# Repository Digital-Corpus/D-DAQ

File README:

D-DAQ
=====
Inspired by a simple, in-cluster, digital boost and EGT gauge created by user Doniol on forums.tdiclub.com.

Features:
3-head, 160x128 OLED displays
14 analog inputs
2 impulse inputs
Data acqusition/logging to microSD card
CAN connectivity
USB connectivity
JTAG header

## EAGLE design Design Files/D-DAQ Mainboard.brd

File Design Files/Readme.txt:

The contents of this zip folder are released under the CERN OHL v1.2
For more information, please visit:
http://www.ohwr.org/projects/cernohl/wiki

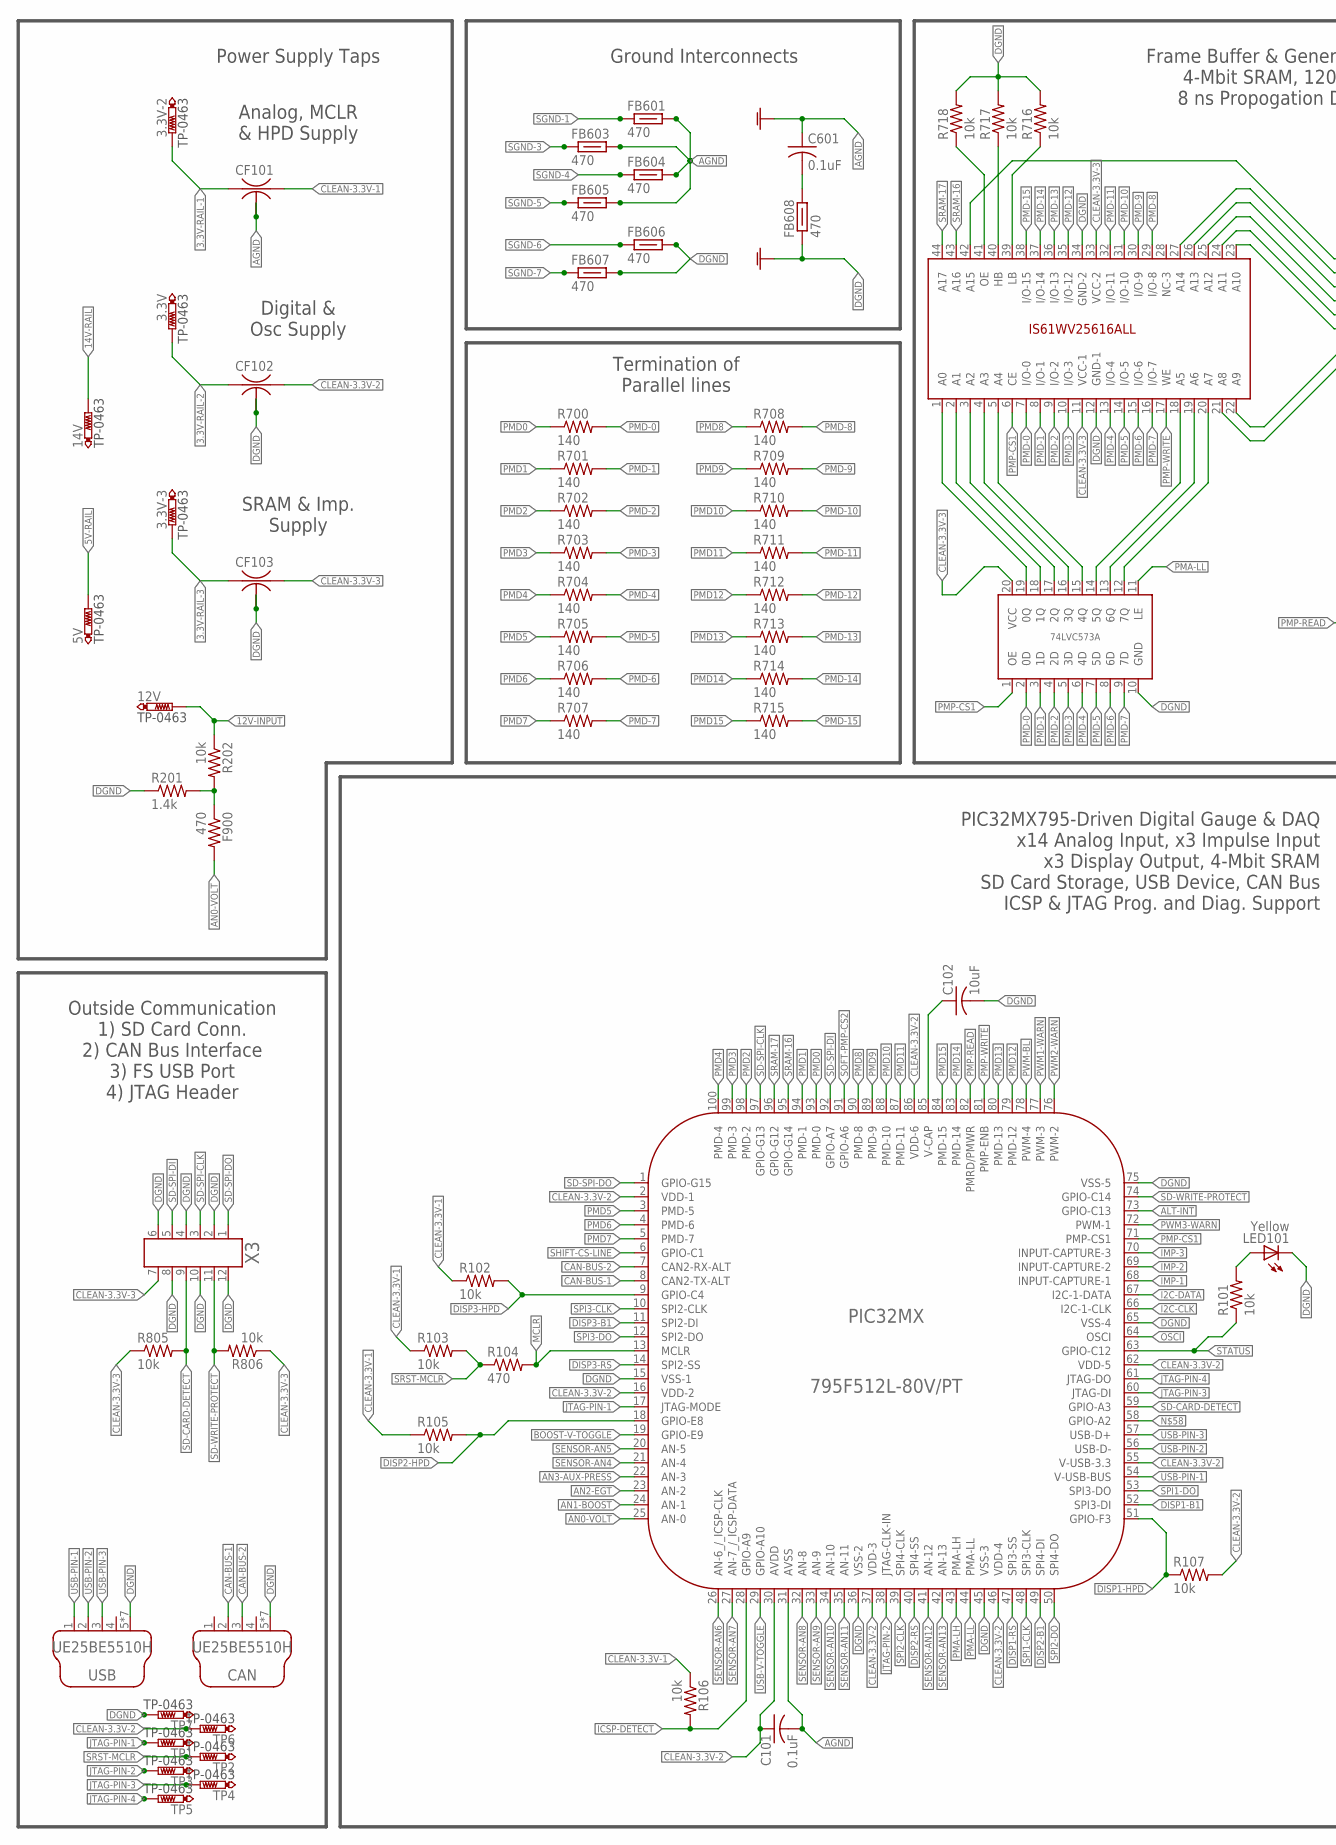
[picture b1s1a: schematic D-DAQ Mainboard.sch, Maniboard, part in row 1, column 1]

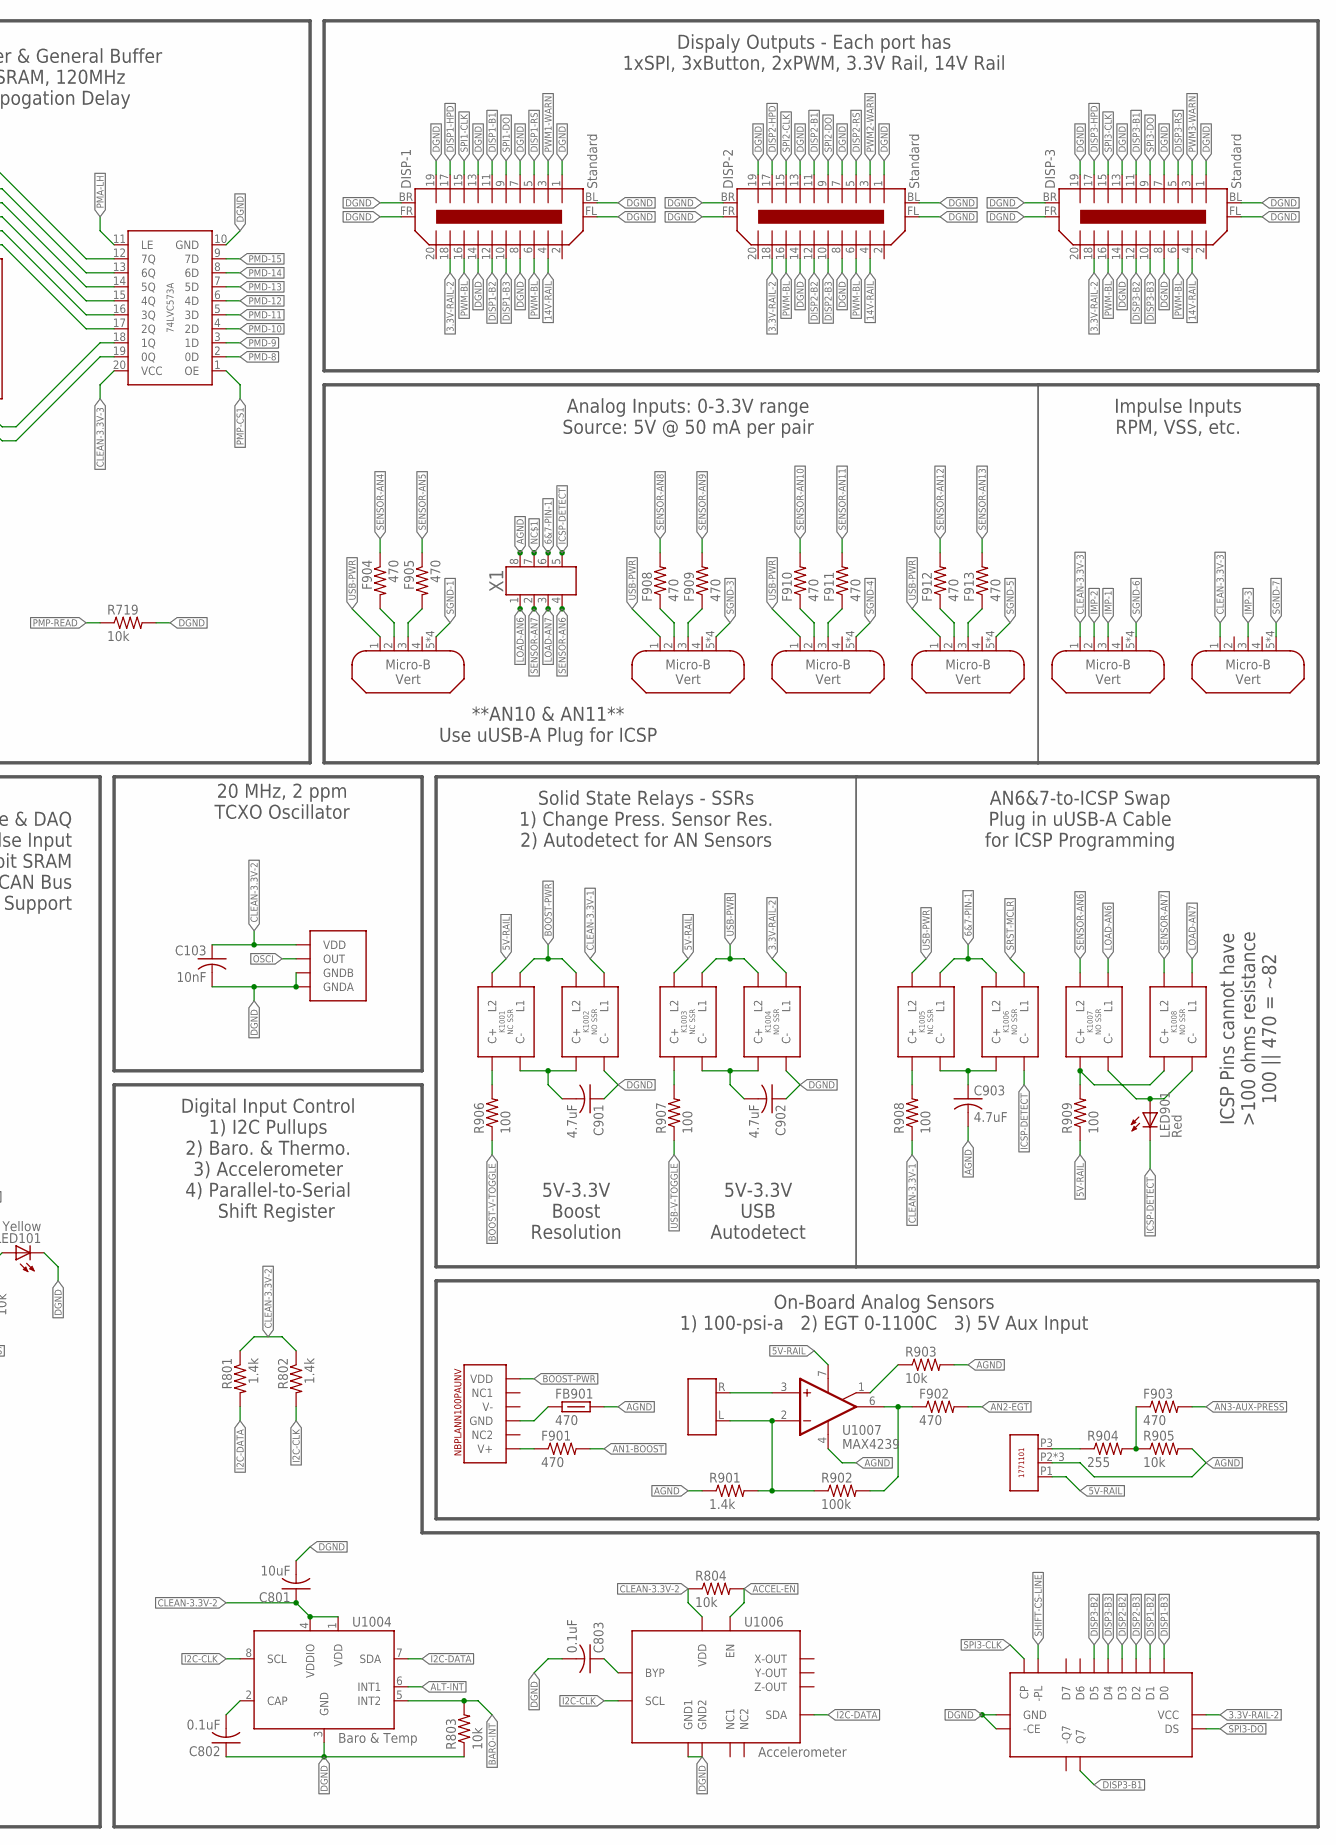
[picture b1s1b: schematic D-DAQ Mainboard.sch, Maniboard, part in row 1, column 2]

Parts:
3.3V, 3.3V-2, 3.3V-3, 5V, 12V, 14V: TP-0463; TP-REC
AUX: PC-3-1771101; PC-1771101
C101, C601, C802, C803: 0.1uF; SMD-0603
C102, C801: 10uF; SMD-0805
C103: 10nF; SMD-0603
C901, C902, C903: 4.7uF; SMD-0603
CAN: UE25BE5510H; USB-MINI-B-VERT
CF101, CF102, CF103: NMF21PS; NFM21PS
DISP-1, DISP-2, DISP-3: Standard; JAE-MDP-STD
EGT: PC-2-1702610; PC-1702610
F900, F901, F902, F903, F904, F905, F908, F909, F910, F911, F912, F913: 470; SMD-0603
FB601, FB603, FB604, FB605, FB606, FB607, FB608, FB901: 470; SMD-0603
IMP-1&2, IMP-3: Micro USB; USB-MICRO-B-VERT
K1001, K1003, K1005: NC SSR; SOP-4-NC
K1002, K1004, K1006, K1007, K1008: NO SSR; SOP-4-NO
LED101: Yellow; SMD-0603
LED901: Red; SMD-0603
MEM1001: IS61WV25616ALL; TSOP-44
P-4&5, P-8&9, P-10&11, P-12&13: Micro USB; USB-MICRO-B-VERT
R101, R102, R103, R105, R106, R107, R202, R716, R717, R718, R719, R803, R804, R805, R806, R903, R905: 10k; SMD-0603
R104: 470; SMD-0603
R201, R801, R802, R901: 1.4k; SMD-0603
R700, R701, R702, R703, R704, R705, R706, R707, R708, R709, R710, R711, R712, R713, R714, R715: 140; SMD-0402
R902: 100k; SMD-0603
R904: 255; SMD-0603
R906, R907, R908, R909: 100; SMD-0603
TP1, TP2, TP3, TP4, TP5, TP6, TP7: TP-0463; TP-REC
U1001: 795F512L-80V/PT; TQFP-100-14X14
U1002, U1003: Octal D-Latch; TSSOP-20
U1004: Baro & Temp; LGA-8
U1005: Boost; LEADLESS-SMT
U1006: Accelerometer; QFN-12
U1007: MAX4239; SOT-8
U1008: NXP-74HC165; DHVQFN16
USB: UE25BE5510H; USB-MINI-B-VERT
X1: MOLEX-87760-0816
X3: MOLEX-87760-1216"; MOLEX-87760-1216
Y1001: XTC7009; 3.2X2.5MM

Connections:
3.3V-RAIL-1: 3.3V-2.TP, CF101.1
3.3V-RAIL-2: 3.3V.TP, CF102.1, DISP-1.18, DISP-2.18, DISP-3.18, K1004.3 (L1), U1008.VCC
3.3V-RAIL-3: 3.3V-3.TP, CF103.1
5V-RAIL: 5V.TP, AUX.P1, K1001.4 (L2), K1003.4 (L2), R909.1, U1007.7 (V+)
6&7-PIN-1: K1005.3 (L1), K1006.4 (L2), X1.6
12V-INPUT: 12V.TP, R202.1
14V-RAIL: 14V.TP, DISP-1.4, DISP-2.4, DISP-3.4
ACCEL-BYP: C803.1, U1006.1 (BYP)
ACCEL-EN: R804.2, U1006.4 (EN)
ADT-1: K1001.1 (C+), R906.2
ADT-2: K1003.1 (C+), R907.2
ADT-3: K1005.1 (C+), R908.2
ADT-4: K1007.1 (C+), K1008.1 (C+), R909.2
AGND: AUX.P2, AUX.T0, AUX.T1, C101.2, C601.1, C903.2, CF101.2@1 (2), CF101.2@2 (2), FB601.2, FB603.2, FB604.2, FB605.2, FB901.2, R901.1, R903.2, R905.2, U1001.31 (AVSS), U1007.4 (V-), X1.8
ALT-INT: U1001.73 (GPIO-C13), U1004.6 (INT1)
AN0-VOLT: F900.2, U1001.25 (AN-0)
AN1-BOOST: F901.2, U1001.24 (AN-1)
AN2-EGT: F902.2, U1001.23 (AN-2)
AN3-AUX-PRESS: F903.2, U1001.22 (AN-3)
AN4: F904.2, P-4&5.2
AN5: F905.2, P-4&5.3
AN8: F908.1, P-8&9.2
AN9: F909.1, P-8&9.3
AN10: F910.1, P-10&11.2
AN11: F911.1, P-10&11.3
AN12: F912.1, P-12&13.2
AN13: F913.1, P-12&13.3
AUX-OUT: F903.1, R904.2, R905.1
BARO-INT: R803.2, U1004.5 (INT2)
BOOST-GND: FB901.1, U1005.4 (GND)
BOOST-OUT: F901.1, U1005.6 (V+)
BOOST-PWR: K1001.3 (L1), K1002.4 (L2), U1005.1 (VDD)
BOOST-SSR: C901.2, K1001.2 (C-), K1002.1 (C+)
BOOST-V-TOGGLE: R906.1, U1001.19 (GPIO-E9)
CAN-BUS-1: CAN.2, U1001.8 (CAN2-TX-ALT)
CAN-BUS-2: CAN.3, U1001.7 (CAN2-RX-ALT)
CLEAN-3.3V-1: CF101.3, K1002.3 (L1), R102.1, R103.1, R105.1, R106.1, R908.1
CLEAN-3.3V-2: C101.1, C103.1, C801.1, CF102.3, R107.2, R801.1, R802.1, R804.1, TP6.TP, U1001.2 (VDD-1), U1001.16 (VDD-2), U1001.30 (AVDD), U1001.37 (VDD-3), U1001.46 (VDD-4), U1001.55 (V-USB-3.3), U1001.62 (VDD-5), U1001.86 (VDD-6), U1004.1 (VDD), U1004.4 (VDDIO), U1006.2 (VDD), Y1001.P$4 (VDD)
CLEAN-3.3V-3: CF103.3, IMP-1&2.1, IMP-3.1, MEM1001.11 (VCC-1), MEM1001.33 (VCC-2), R805.1, R806.1, U1002.20 (VCC), U1003.20 (VCC), X3.7
DGND: C102.2, C103.2, C801.2, C802.1, C803.2, C901.1, C902.1, CAN.5, CAN.P$1, CAN.P$2, CAN.P$3, CAN.P$4, CAN.T0, CAN.T1, CF102.2@1 (2), CF102.2@2 (2), CF103.2@1 (2), CF103.2@2 (2), DISP-1.1, DISP-1.7, DISP-1.8, DISP-1.13, DISP-1.14, DISP-1.19, DISP-1.BL, DISP-1.BR, DISP-1.FL, DISP-1.FR, DISP-2.1, DISP-2.7, DISP-2.8, DISP-2.13, DISP-2.14, DISP-2.19, DISP-2.BL, DISP-2.BR, DISP-2.FL, DISP-2.FR, DISP-3.1, DISP-3.7, DISP-3.8, DISP-3.13, DISP-3.14, DISP-3.19, DISP-3.BL, DISP-3.BR, DISP-3.FL, DISP-3.FR, FB606.2, FB607.2, FB608.1, K1002.2 (C-), K1004.2 (C-), LED101.2, MEM1001.12 (GND-1), MEM1001.34 (GND-2), R201.1, R716.2, R717.2, R718.2, R719.2, R803.1, TP7.TP, U1001.15 (VSS-1), U1001.36 (VSS-2), U1001.45 (VSS-3), U1001.65 (VSS-4), U1001.75 (VSS-5), U1002.10 (GND), U1003.10 (GND), U1004.3 (GND), U1006.6 (GND1), U1006.7 (GND2), U1008.-CE, U1008.GND, U1008.GND2 (GND), USB.5, USB.P$1, USB.P$2, USB.P$3, USB.P$4, USB.T0, USB.T1, X3.2, X3.4, X3.6, X3.8, X3.10, X3.12, Y1001.P$1 (GNDA), Y1001.P$2 (GNDB)
DISP1-B1: DISP-1.11, U1001.52 (SPI3-DI)
DISP1-B2: DISP-1.12, U1008.D1
DISP1-B3: DISP-1.10, U1008.D0
DISP1-HPD: DISP-1.17, R107.1, U1001.51 (GPIO-F3)
DISP1-RS: DISP-1.5, U1001.47 (SPI3-SS)
DISP2-B1: DISP-2.11, U1001.49 (SPI4-DI)
DISP2-B2: DISP-2.12, U1008.D3
DISP2-B3: DISP-2.10, U1008.D2
DISP2-HPD: DISP-2.17, R105.2, U1001.18 (GPIO-E8)
DISP2-RS: DISP-2.5, U1001.40 (SPI4-SS)
DISP3-B1: DISP-3.11, U1001.11 (SPI2-DI), U1008.Q7
DISP3-B2: DISP-3.12, U1008.D5
DISP3-B3: DISP-3.10, U1008.D4
DISP3-HPD: DISP-3.17, R102.2, U1001.9 (GPIO-C4)
DISP3-RS: DISP-3.5, U1001.14 (SPI2-SS)
EGT-NEG-IN: EGT.L, R901.2, R902.1, U1007.2 (-IN)
EGT-OUT: F902.1, R902.2, U1007.6 (OUT1)
EGT-POS-IN: EGT.R, U1007.3 (+IN)
EGT-SHDN: R903.1, U1007.1 (CRETN)
GND-FILTER: C601.2, FB608.2
HB-PD: MEM1001.40 (HB), R717.1
I2C-CLK: R802.2, U1001.66 (I2C-1-CLK), U1004.8 (SCL), U1006.5 (SCL)
I2C-DATA: R801.2, U1001.67 (I2C-1-DATA), U1004.7 (SDA), U1006.3 (SDA)
ICSP-DETECT: K1006.2 (C-), LED901.2, R106.2, U1001.28 (GPIO-A9), X1.5
ICSP-LED: K1007.2 (C-), K1008.2 (C-), LED901.1
ICSP-SSR: C903.1, K1005.2 (C-), K1006.1 (C+)
IMP-1: IMP-1&2.3, U1001.68 (INPUT-CAPTURE-1)
IMP-2: IMP-1&2.2, U1001.69 (INPUT-CAPTURE-2)
IMP-3: IMP-3.3, U1001.70 (INPUT-CAPTURE-3)
INPUT-V-SENSE: F900.1, R201.2, R202.2
JTAG-PIN-1: TP1.TP, U1001.17 (JTAG-MODE)
JTAG-PIN-2: TP3.TP, U1001.38 (JTAG-CLK-IN)
JTAG-PIN-3: TP4.TP, U1001.60 (JTAG-DI)
JTAG-PIN-4: TP5.TP, U1001.61 (JTAG-DO)
LB-PD: MEM1001.39 (LB), R716.1
LOAD-AN6: K1007.3 (L1), X1.1
LOAD-AN7: K1008.3 (L1), X1.3
MCLR: R104.2, U1001.13 (MCLR)
MPL-BYP-CAP: C802.2, U1004.2 (CAP)
NC$1: X1.7
OE-PD: MEM1001.41 (OE), R718.1
OIL-PRESS-OUT: AUX.P3, R904.1
OSCI: U1001.64 (OSCI), Y1001.P$3 (OUT)
P$1: CAN.1
PMA-LH: U1001.43 (PMA-LH), U1003.11 (LE)
PMA-LL: U1001.44 (PMA-LL), U1002.11 (LE)
PMD0: R700.1, U1001.93 (PMD-0)
PMD1: R701.1, U1001.94 (PMD-1)
PMD2: R702.1, U1001.98 (PMD-2)
PMD3: R703.1, U1001.99 (PMD-3)
PMD4: R704.1, U1001.100 (PMD-4)
PMD5: R705.1, U1001.3 (PMD-5)
PMD6: R706.1, U1001.4 (PMD-6)
PMD7: R707.1, U1001.5 (PMD-7)
PMD8: R708.1, U1001.90 (PMD-8)
PMD9: R709.1, U1001.89 (PMD-9)
PMD10: R710.1, U1001.88 (PMD-10)
PMD11: R711.1, U1001.87 (PMD-11)
PMD12: R712.1, U1001.79 (PMD-12)
PMD13: R713.1, U1001.80 (PMD-13)
PMD14: R714.1, U1001.83 (PMD-14)
PMD15: R715.1, U1001.84 (PMD-15)
PMD-0: MEM1001.7 (I/O-0), R700.2, U1002.2 (0D)
PMD-1: MEM1001.8 (I/O-1), R701.2, U1002.3 (1D)
PMD-2: MEM1001.9 (I/O-2), R702.2, U1002.4 (2D)
PMD-3: MEM1001.10 (I/O-3), R703.2, U1002.5 (3D)
PMD-4: MEM1001.13 (I/O-4), R704.2, U1002.6 (4D)
PMD-5: MEM1001.14 (I/O-5), R705.2, U1002.7 (5D)
PMD-6: MEM1001.15 (I/O-6), R706.2, U1002.8 (6D)
PMD-7: MEM1001.16 (I/O-7), R707.2, U1002.9 (7D)
PMD-8: MEM1001.29 (I/O-8), R708.2, U1003.2 (0D)
PMD-9: MEM1001.30 (I/O-9), R709.2, U1003.3 (1D)
PMD-10: MEM1001.31 (I/O-10), R710.2, U1003.4 (2D)
PMD-11: MEM1001.32 (I/O-11), R711.2, U1003.5 (3D)
PMD-12: MEM1001.35 (I/O-12), R712.2, U1003.6 (4D)
PMD-13: MEM1001.36 (I/O-13), R713.2, U1003.7 (5D)
PMD-14: MEM1001.37 (I/O-14), R714.2, U1003.8 (6D)
PMD-15: MEM1001.38 (I/O-15), R715.2, U1003.9 (7D)
PMP-CS1: MEM1001.6 (CE), U1001.71 (PMP-CS1), U1002.1 (OE), U1003.1 (OE)
PMP-READ: R719.1, U1001.82 (PMRD/PMWR)
PMP-WRITE: MEM1001.17 (WE), U1001.81 (PMP-ENB)
PWM1-WARN: DISP-1.3, U1001.77 (PWM-3)
PWM2-WARN: DISP-2.3, U1001.76 (PWM-2)
PWM3-WARN: DISP-3.3, U1001.72 (PWM-1)
PWM-BL: DISP-1.6, DISP-1.16, DISP-2.6, DISP-2.16, DISP-3.6, DISP-3.16, U1001.78 (PWM-4)
SD-CARD-DETECT: R805.2, U1001.59 (GPIO-A3), X3.9
SD-SPI-CLK: U1001.97 (GPIO-G13), X3.3
SD-SPI-DI: U1001.92 (GPIO-A7), X3.5
SD-SPI-DO: U1001.1 (GPIO-G15), X3.1
SD-WRITE-PROTECT: R806.2, U1001.74 (GPIO-C14), X3.11
SENSOR-AN4: F904.1, U1001.21 (AN-4)
SENSOR-AN5: F905.1, U1001.20 (AN-5)
SENSOR-AN6: K1007.4 (L2), U1001.26 (AN-6_/_ICSP-CLK), X1.4
SENSOR-AN7: K1008.4 (L2), U1001.27 (AN-7_/_ICSP-DATA), X1.2
SENSOR-AN8: F908.2, U1001.32 (AN-8)
SENSOR-AN9: F909.2, U1001.33 (AN-9)
SENSOR-AN10: F910.2, U1001.34 (AN-10)
SENSOR-AN11: F911.2, U1001.35 (AN-11)
SENSOR-AN12: F912.2, U1001.41 (AN-12)
SENSOR-AN13: F913.2, U1001.42 (AN-13)
SGND-1: FB601.1, P-4&5.5, P-4&5.T0 (5), P-4&5.T1 (5), P-4&5.T2 (5)
SGND-3: FB603.1, P-8&9.5, P-8&9.T0 (5), P-8&9.T1 (5), P-8&9.T2 (5)
SGND-4: FB604.1, P-10&11.5, P-10&11.T0 (5), P-10&11.T1 (5), P-10&11.T2 (5)
SGND-5: FB605.1, P-12&13.5, P-12&13.T0 (5), P-12&13.T1 (5), P-12&13.T2 (5)
SGND-6: FB606.1, IMP-1&2.5, IMP-1&2.T0 (5), IMP-1&2.T1 (5), IMP-1&2.T2 (5)
SGND-7: FB607.1, IMP-3.5, IMP-3.T0 (5), IMP-3.T1 (5), IMP-3.T2 (5)
SHIFT-CS-LINE: U1001.6 (GPIO-C1), U1008.-PL
SOFT-PMP-CS2: U1001.91 (GPIO-A6)
SPI1-CLK: DISP-1.15, U1001.48 (SPI3-CLK)
SPI1-DO: DISP-1.9, U1001.53 (SPI3-DO)
SPI2-CLK: DISP-2.15, U1001.39 (SPI4-CLK)
SPI2-DO: DISP-2.9, U1001.50 (SPI4-DO)
SPI3-CLK: DISP-3.15, U1001.10 (SPI2-CLK), U1008.CP
SPI3-DO: DISP-3.9, U1001.12 (SPI2-DO), U1008.DS
SRAM-0: MEM1001.1 (A0), U1002.19 (0Q)
SRAM-1: MEM1001.2 (A1), U1002.18 (1Q)
SRAM-2: MEM1001.3 (A2), U1002.17 (2Q)
SRAM-3: MEM1001.4 (A3), U1002.16 (3Q)
SRAM-4: MEM1001.5 (A4), U1002.15 (4Q)
SRAM-5: MEM1001.18 (A5), U1002.14 (5Q)
SRAM-6: MEM1001.19 (A6), U1002.13 (6Q)
SRAM-7: MEM1001.20 (A7), U1002.12 (7Q)
SRAM-8: MEM1001.21 (A8), U1003.19 (0Q)
SRAM-9: MEM1001.22 (A9), U1003.18 (1Q)
SRAM-10: MEM1001.23 (A10), U1003.17 (2Q)
SRAM-11: MEM1001.24 (A11), U1003.16 (3Q)
SRAM-12: MEM1001.25 (A12), U1003.15 (4Q)
SRAM-13: MEM1001.26 (A13), U1003.14 (5Q)
SRAM-14: MEM1001.27 (A14), U1003.13 (6Q)
SRAM-15: MEM1001.42 (A15), U1003.12 (7Q)
SRAM-16: MEM1001.43 (A16), U1001.95 (GPIO-G14)
SRAM-17: MEM1001.44 (A17), U1001.96 (GPIO-G12)
SRST-MCLR: K1006.3 (L1), R103.2, R104.1, TP2.TP
STATUS: R101.1, U1001.63 (GPIO-C12)
STATUS-LED: LED101.1, R101.2
USB-PIN-1: U1001.54 (V-USB-BUS), USB.1
USB-PIN-2: U1001.56 (USB-D-), USB.2
USB-PIN-3: U1001.57 (USB-D+), USB.3
USB-PWR: K1003.3 (L1), K1004.4 (L2), K1005.4 (L2), P-4&5.1, P-8&9.1, P-10&11.1, P-12&13.1
USB-SSR: C902.2, K1003.2 (C-), K1004.1 (C+)
USB-V-TOGGLE: R907.1, U1001.29 (GPIO-A10)
V-CAP: C102.1, U1001.85 (V-CAP)

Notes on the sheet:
Power Supply Taps
Frame Buffer & General Buffer 4-Mbit SRAM, 120MHz 8 ns Propogation Delay
5V-3.3V Boost Resolution
5V-3.3V USB Autodetect
AN6&7-to-ICSP Swap Plug in uUSB-A Cable for ICSP Programming
Dispaly Outputs - Each port has 1xSPI, 3xButton, 2xPWM, 3.3V Rail, 14V Rail
Ground Interconnects
Analog Inputs: 0-3.3V range Source: 5V @ 50 mA per pair
**AN10 & AN11** Use uUSB-A Plug for ICSP
Solid State Relays - SSRs 1) Change Press. Sensor Res. 2) Autodetect for AN Sensors
Impulse Inputs RPM, VSS, etc.
ICSP Pins cannot have >100 ohms resistance 100 || 470 = ~82
Termination of Parallel lines
Outside Communication 1) SD Card Conn. 2) CAN Bus Interface 3) FS USB Port 4) JTAG Header
20 MHz, 2 ppm TCXO Oscillator
On-Board Analog Sensors 1) 100-psi-a 2) EGT 0-1100C 3) 5V Aux Input
Digital Input Control 1) I2C Pullups 2) Baro. & Thermo. 3) Accelerometer 4) Parallel-to-Serial Shift Register
PIC32MX795-Driven Digital Gauge & DAQ x14 Analog Input, x3 Impulse Input x3 Display Output, 4-Mbit SRAM SD Card Storage, USB Device, CAN Bus ICSP & JTAG Prog. and Diag. Support
Digital & Osc Supply
Analog, MCLR & HPD Supply
SRAM & Imp. Supply

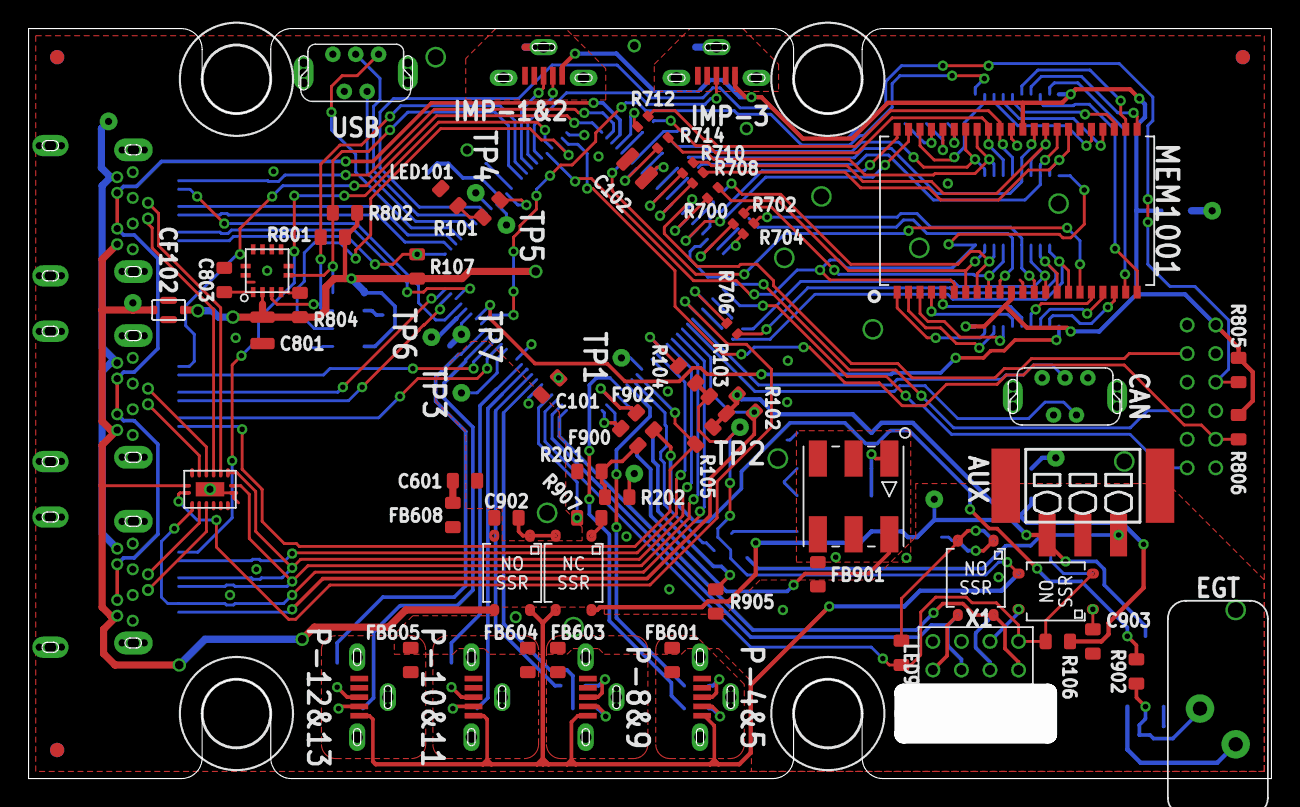
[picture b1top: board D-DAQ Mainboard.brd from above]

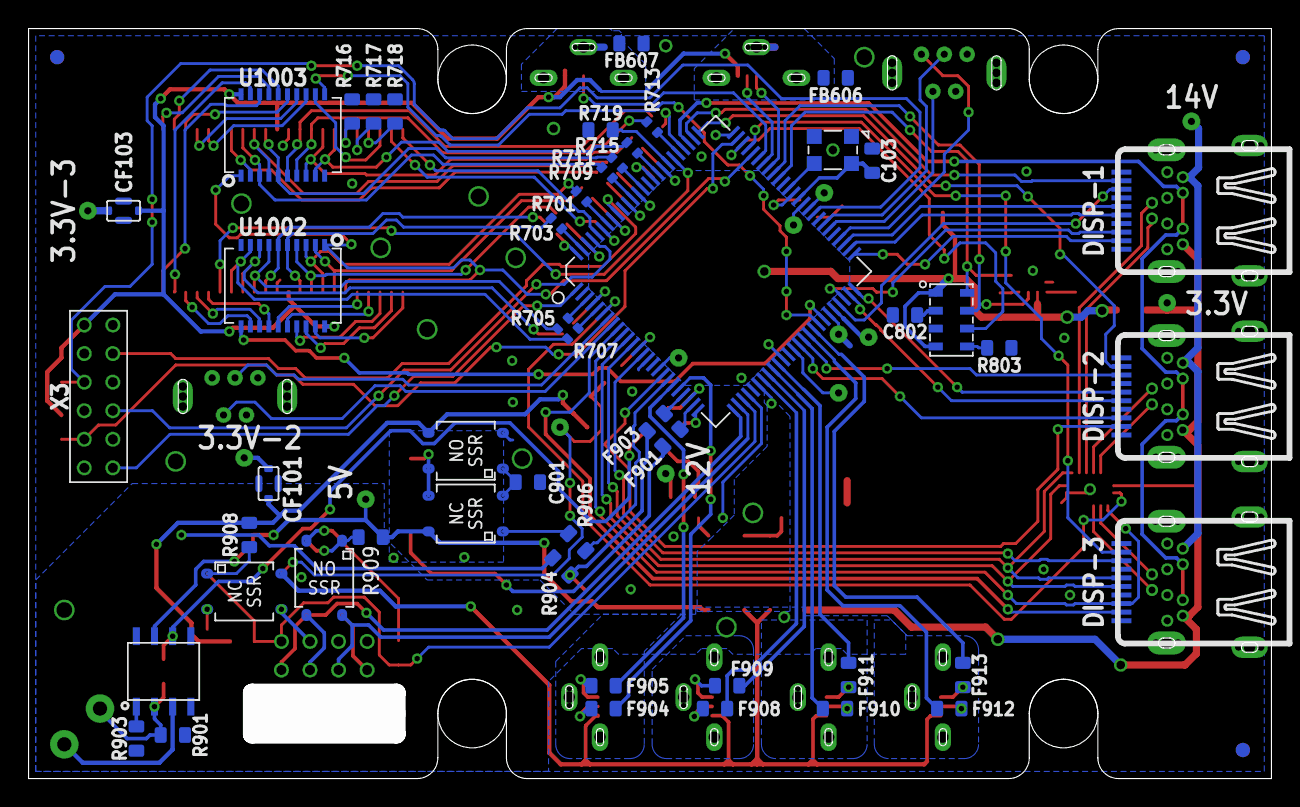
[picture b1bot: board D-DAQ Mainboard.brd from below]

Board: 2 copper layers, 87.0 x 52.5 mm, 137 parts (60 on the bottom side), 179 nets.

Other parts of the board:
BFID-1, BFID-2, BFID-3: 1MM-FIDUCIAL
HOLE-BL: 3.2-GRMT
HOLE-BR: 3.2-GRMT
HOLE-ML: 3.2-GRMT
HOLE-MR: 3.2-GRMT
OSHW-BOT: OSHW-LOGO-L
OSHW-TOP: OSHW-LOGO-L
TFID-1, TFID-2, TFID-3: 1MM-FIDUCIAL

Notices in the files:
Design Files/D-DAQ Mainboard.sch:
Released Under CERN OHL v1.2
parts and their libraries:
SparkFun: Licensing: CC v3.0 Share-Alike You are welcome to use this library for commercial purposes.
